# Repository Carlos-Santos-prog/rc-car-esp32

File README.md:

# RC Car ESP32 🏎️

**Vehículo RC de combate con seguimiento de línea, controlado por ESP32.**

Proyecto final del **Laboratorio de Electrónica II** del Instituto Tecnológico de las Américas (ITLA). Este repositorio reúne el diseño electrónico completo —esquemático, PCB, BOM y documentación— y servirá también como base para el firmware del vehículo.

---

## 📋 Descripción

El carrito combina dos modos de operación:

- **Seguidor de línea:** dos sensores ópticos CNY70 detectan el trazado y el ESP32 corrige la trayectoria en tiempo real.
- **Funciones de batalla:** servos para barrera y pala, luces direccionales intermitentes y bocina, pensados para competencias entre vehículos.

La etapa de potencia maneja **cuatro motores DC de forma independiente** mediante cuatro puentes H con MOSFETs, aislados por optoacopladores para proteger la lógica del ESP32.

## ✨ Características

- Control central con **ESP32 DevKitC V4**.
- **4 puentes H** independientes (IRF3205 + IRF9540N) para tracción 4WD.
- Aislamiento de señal de los puentes H con **optoacopladores PC817**.
- **2 sensores de línea CNY70** para seguimiento de pista.
- **3 servos** (barrera, pala y dirección auxiliar).
- **Luces direccionales** izquierda/derecha e intermitentes.
- **Bocina** con amplificador de audio **TDA2003**.
- Fuentes reguladas para lógica y servos: **LM7805**, **LM317** y rieles de +15 V, +7.5 V, +5 V y +3.3 V.
- PCB de **2 capas**, **80 × 130 mm**, con conectores JST EH para periféricos.

## 🧩 Arquitectura de hardware

| Bloque | Componentes principales |
|---|---|
| Control lógico | ESP32-DevKitC, MMBT3904, resistencias de pull-up |
| Seguidor de línea | 2 × CNY70 |
| Puentes H | 4 × IRF3205 (N), 4 × IRF9540N (P), 6 × PC817 |
| Servos | 3 × conectores JST EH de 3 pines |
| Luces | LED direccionales e intermitentes |
| Audio | TDA2003 + parlante (conector BOCINA) |
| Alimentación | LM7805, LM317, LM317 ajustable, capacitores de filtrado |
| Conectores | Batería principal, batería auxiliar, 4 motores, 3 servos, bocina, LEDs |

## 📁 Estructura del repositorio

```text
.
├── electronic_design_kicad/          # Diseño electrónico (KiCad 10)
│   ├── ProyectoFinalCarrito2.kicad_pro
│   ├── ProyectoFinalCarrito2.kicad_sch
│   ├── ProyectoFinalCarrito2.kicad_pcb
│   ├── ProyectoFinalCarrito2.csv     # Lista de materiales (BOM)
│   ├── ProyectoFinalCarrito2-schematic.pdf
│   ├── fabrication-toolkit-options.json
│   ├── docs/
│   │   └── esp32_devkitC_v4_pinlayout.png
│   └── README.md
├── .gitignore
├── .gitattributes
├── LICENSE
└── README.md
```

## 🚀 Cómo abrir el proyecto

1. Instala **KiCad 10.0** o superior.
2. Abre `electronic_design_kicad/ProyectoFinalCarrito2.kicad_pro`.
3. Desde KiCad puedes revisar:
   - **Esquemático** → `ProyectoFinalCarrito2.kicad_sch`
   - **PCB** → `ProyectoFinalCarrito2.kicad_pcb`
   - **ERC/DRC** para validar el diseño antes de fabricar.

> Los archivos conservan el nombre original del proyecto (`ProyectoFinalCarrito2`) para no romper las referencias internas entre hoja, placa y proyecto en KiCad.

## 🏭 Fabricación

- La **BOM** está en `electronic_design_kicad/ProyectoFinalCarrito2.csv`.
- El **esquemático en PDF** está en `electronic_design_kicad/ProyectoFinalCarrito2-schematic.pdf`.
- Los Gerbers se pueden generar con el plugin **Fabrication Toolkit** usando la configuración incluida (`fabrication-toolkit-options.json`).

## 🗺️ Roadmap

- [x] Diseño electrónico (esquemático + PCB)
- [ ] Firmware del ESP32 (control de motores, sensores y servos)
- [ ] Validación del prototipo y ajuste de PID del seguidor de línea
- [ ] Diseño de carcasa / estructura 3D
- [ ] Documentación de montaje y pruebas

## 📄 Licencia

Este proyecto se distribuye bajo la licencia **MIT**. Consulta [LICENSE](LICENSE) para más detalles.

## 👤 Autor

**Carlos Alexander Arias Santos**
Instituto Tecnológico de las Américas (ITLA) — Laboratorio de Electrónica II

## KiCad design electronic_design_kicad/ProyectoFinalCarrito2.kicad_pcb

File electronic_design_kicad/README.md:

# Diseño electrónico — RC Car ESP32

Diseño completo en **KiCad 10.0** del vehículo RC de combate con seguimiento de línea basado en ESP32.

## Contenido

| Archivo | Descripción |
|---|---|
| `ProyectoFinalCarrito2.kicad_pro` | Proyecto KiCad (abrir este archivo) |
| `ProyectoFinalCarrito2.kicad_sch` | Esquemático |
| `ProyectoFinalCarrito2.kicad_pcb` | Placa de circuito impreso (2 capas, 80 × 130 mm) |
| `ProyectoFinalCarrito2.csv` | Lista de materiales (BOM) |
| `ProyectoFinalCarrito2-schematic.pdf` | Esquemático exportado a PDF |
| `fabrication-toolkit-options.json` | Configuración del plugin Fabrication Toolkit |
| `docs/esp32_devkitC_v4_pinlayout.png` | Pinout de referencia del ESP32 DevKitC V4 |

## Bloques del diseño

- **Control lógico / ESP32:** ESP32-DevKitC V4 y etapa de acoplamiento con transistores MMBT3904.
- **Seguidor de línea:** 2 sensores ópticos CNY70.
- **Puentes H:** 4 etapas independientes con IRF3205 / IRF9540N y aislamiento por PC817.
- **Funciones de batalla:** 3 servos, luces direccionales e intermitentes y bocina con TDA2003.
- **Alimentación:** LM7805, LM317 y rieles de +15 V, +7.5 V, +5 V y +3.3 V.

## Notas

- Los archivos conservan el nombre original del proyecto para mantener las referencias internas de KiCad.
- `ProyectoFinalCarrito2.kicad_prl` y `fp-info-cache` son archivos locales de KiCad y están excluidos del repositorio mediante `.gitignore`.
- Las copias de seguridad automáticas (`*-backups/`) se conservan localmente, pero no se versionan.
- Antes de fabricar, ejecuta **ERC** y **DRC** en KiCad y genera los Gerbers con Fabrication Toolkit.

## Cómo abrir

1. Abre KiCad 10.0 o superior.
2. Selecciona `ProyectoFinalCarrito2.kicad_pro`.
3. Revisa el esquemático y la PCB desde el administrador de proyectos.

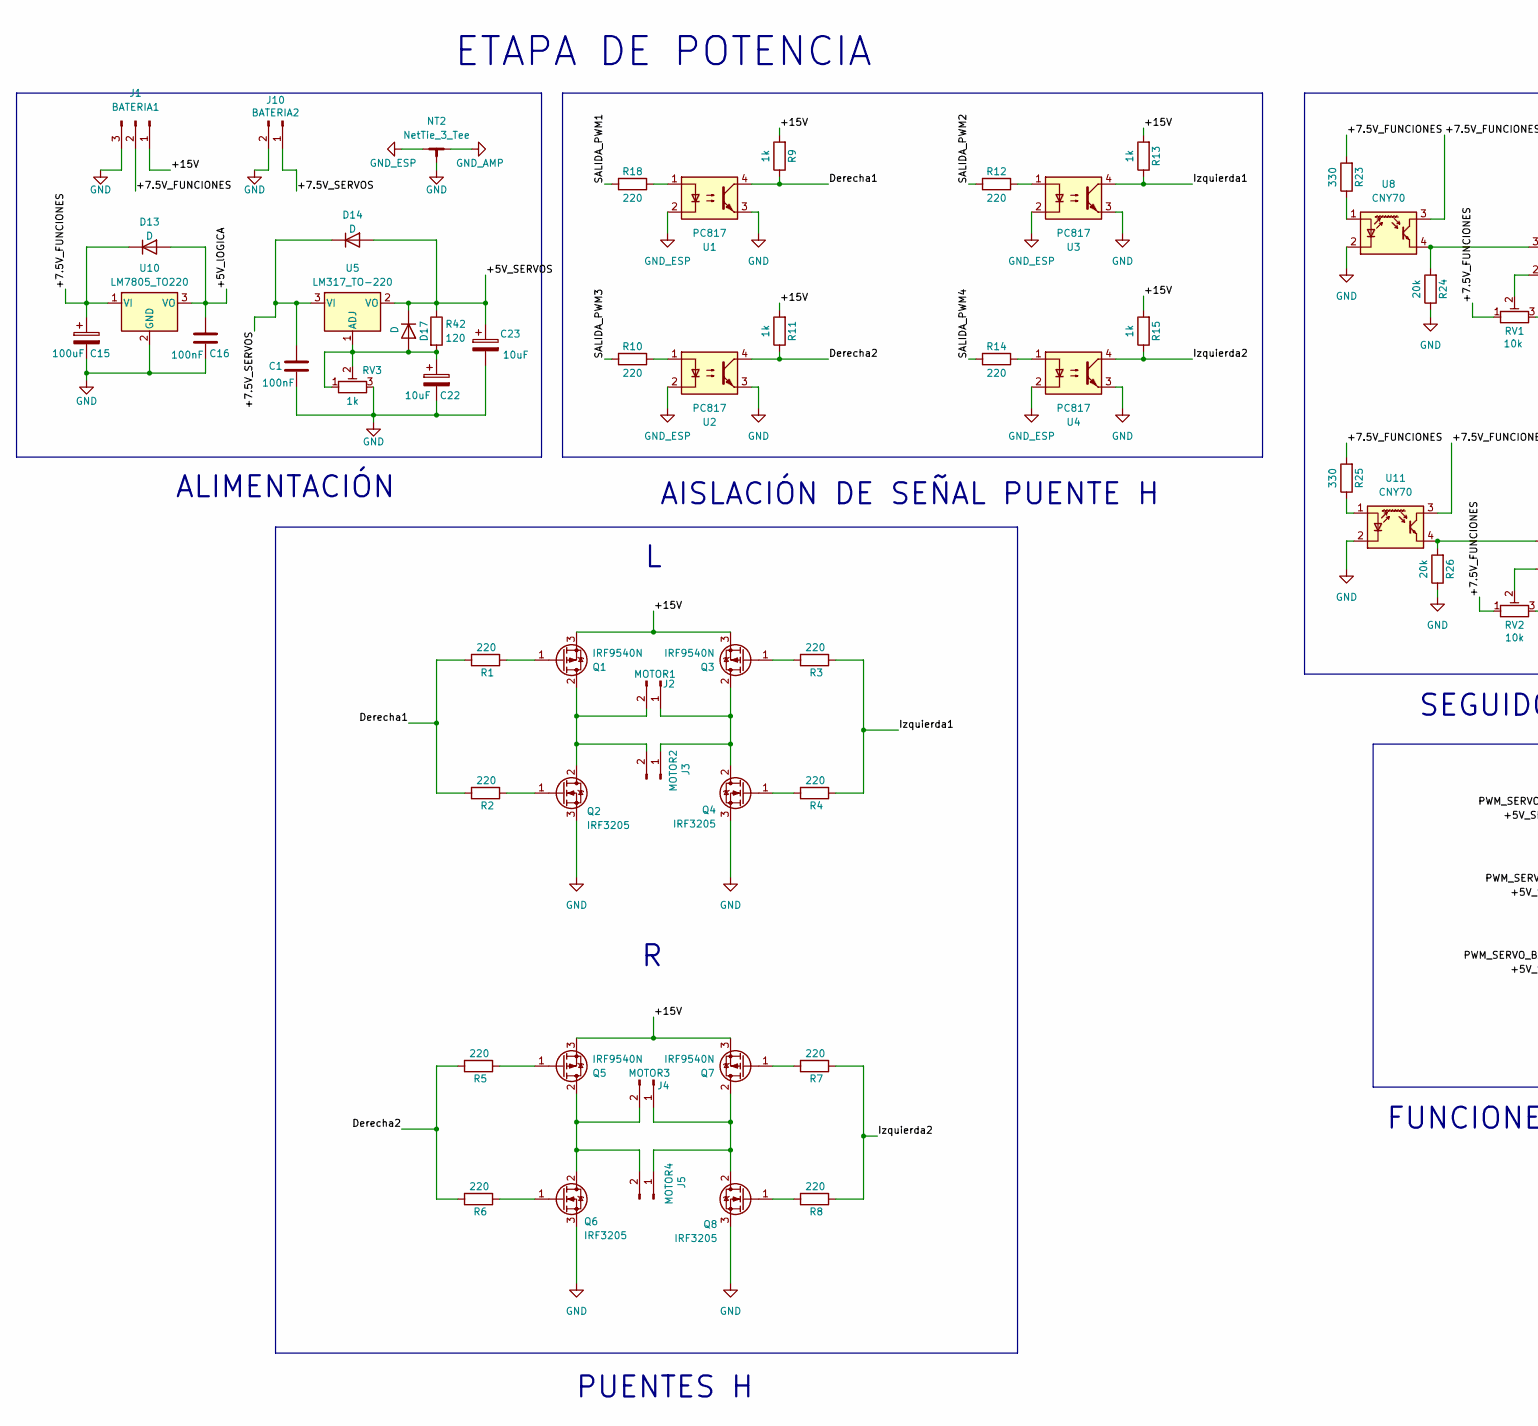
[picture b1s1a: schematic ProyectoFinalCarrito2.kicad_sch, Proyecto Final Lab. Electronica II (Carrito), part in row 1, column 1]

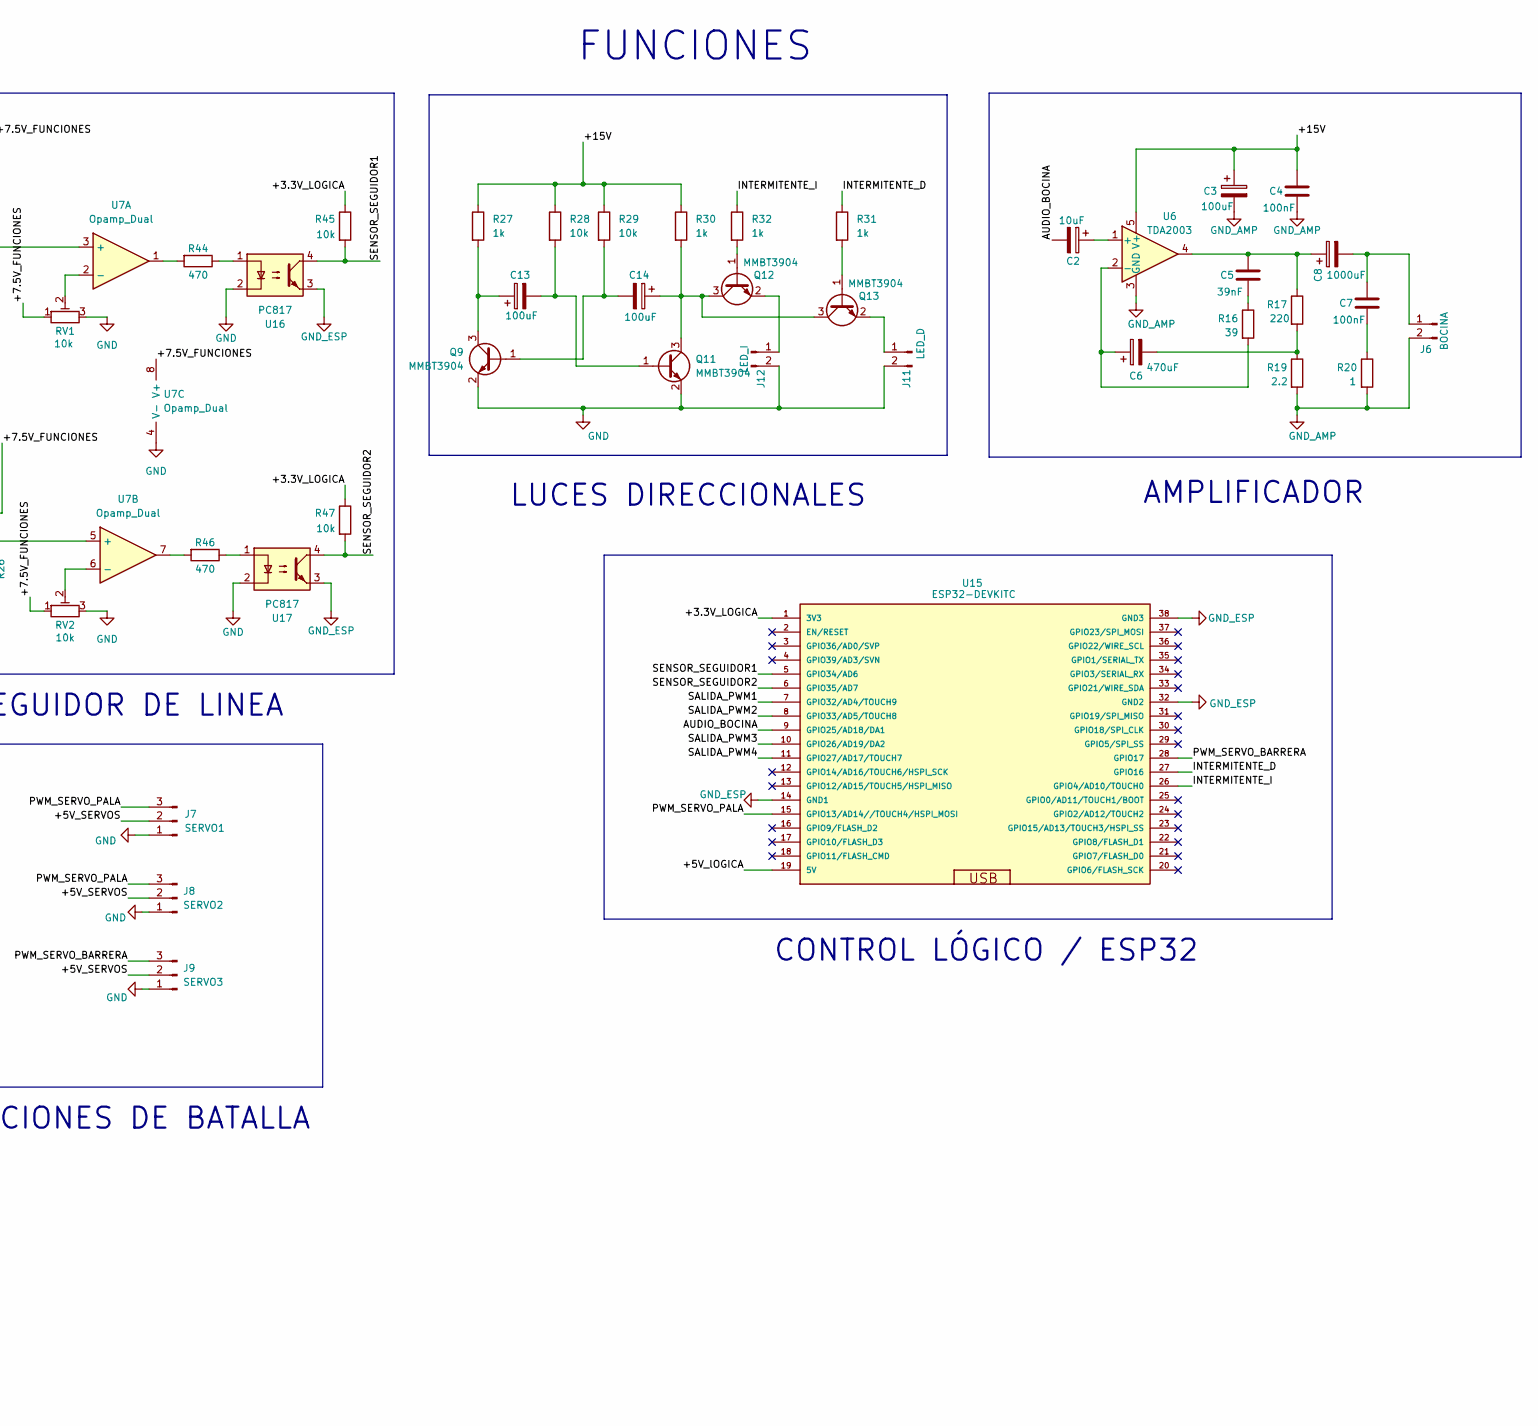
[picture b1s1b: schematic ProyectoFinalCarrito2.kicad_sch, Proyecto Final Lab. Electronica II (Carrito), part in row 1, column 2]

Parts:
C1, C4, C7, C16: 100nF; C_0805_2012Metric
C2, C22, C23: 10uF; CP_Radial_D5.0mm_P2.00mm
C3, C13, C14, C15: 100uF; CP_Radial_D8.0mm_P3.80mm
C5: 39nF; C_0805_2012Metric
C6: 470uF; CP_Radial_D10.0mm_P5.00mm
C8: 1000uF; CP_Radial_D10.0mm_P5.00mm
D13, D14, D17: D; D_SOD-123
J1: BATERIA1; JST_EH_B3B-EH-A_1x03_P2.50mm_Vertical
J2: MOTOR1; JST_EH_B2B-EH-A_1x02_P2.50mm_Vertical
J3: MOTOR2; JST_EH_B2B-EH-A_1x02_P2.50mm_Vertical
J4: MOTOR3; JST_EH_B2B-EH-A_1x02_P2.50mm_Vertical
J5: MOTOR4; JST_EH_B2B-EH-A_1x02_P2.50mm_Vertical
J6: BOCINA; JST_EH_B2B-EH-A_1x02_P2.50mm_Vertical
J7: SERVO1; JST_EH_B3B-EH-A_1x03_P2.50mm_Vertical
J8: SERVO2; JST_EH_B3B-EH-A_1x03_P2.50mm_Vertical
J9: SERVO3; JST_EH_B3B-EH-A_1x03_P2.50mm_Vertical
J10: BATERIA2; JST_EH_B2B-EH-A_1x02_P2.50mm_Vertical
J11: LED_D; JST_EH_B2B-EH-A_1x02_P2.50mm_Vertical
J12: LED_I; JST_EH_B2B-EH-A_1x02_P2.50mm_Vertical
NT2: NetTie_3_Tee; NetTie-3_SMD_Pad2.0mm
Q1, Q3, Q5, Q7: IRF9540N; TO-220-3_Vertical
Q2, Q4, Q6, Q8: IRF3205; TO-220-3_Vertical
Q9, Q11, Q12, Q13: MMBT3904; SOT-23
R1, R2, R3, R4, R5, R6, R7, R8: 220; R_Axial_DIN0207_L6.3mm_D2.5mm_P10.16mm_Horizontal
R9, R11, R13, R15: 1k; R_Axial_DIN0207_L6.3mm_D2.5mm_P10.16mm_Horizontal
R10, R12, R14, R17, R18: 220; R_0805_2012Metric
R16: 39; R_0805_2012Metric
R19: 2.2; R_0805_2012Metric
R20: 1; R_1206_3216Metric
R23, R25: 330; R_0805_2012Metric
R24, R26: 20k; R_0805_2012Metric
R27, R30, R31, R32: 1k; R_0805_2012Metric
R28, R29, R45, R47: 10k; R_0805_2012Metric
R42: 120; R_0805_2012Metric
R44, R46: 470; R_0805_2012Metric
RV1, RV2: 10k; Potentiometer_Bourns_3266W_Vertical
RV3: 1k; Potentiometer_Bourns_3266W_Vertical
U1, U2, U3, U4, U16, U17: PC817; DIP-4_W7.62mm
U5: LM317_TO-220; TO-220-3_Vertical
U6: TDA2003; TO-220-5_P3.4x3.7mm_StaggerOdd_Lead3.8mm_Vertical
U7: Opamp_Dual; SOIC-8_3.9x4.9mm_P1.27mm
U8, U11: CNY70; Vishay_CNY70
U10: LM7805_TO220; TO-220-3_Vertical
U15: ESP32-DEVKITC

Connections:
/+3.3V_LOGICA: R45.1, R47.1, U15.1 (3V3)
/+5V_SERVOS: C23.1, D14.2 (A), D17.1 (K), J7.2, J8.2, J9.2, R42.1, U5.2 (VO)
/+5V_lOGICA: C16.2, D13.2 (A), U10.3 (VO), U15.19 (5V)
/+7.5V_FUNCIONES: C15.1, D13.1 (K), J1.2, R23.2, R25.2, RV1.1, RV2.1, U7.8 (V+), U8.3 (C), U10.1 (VI), U11.3 (C)
/+7.5V_SERVOS: C1.2, D14.1 (K), J10.1, U5.3 (VI)
/+15V: C3.1, C4.2, J1.1, Q1.3 (S), Q3.3 (S), Q5.3 (S), Q7.3 (S), R9.2, R11.2, R13.2, R15.2, R27.1, R28.1, R29.1, R30.1, U6.5 (V+)
/AUDIO_BOCINA: C2.2, U15.9 (GPIO25/AD18/DA1)
/Derecha1: R1.2, R2.2, R9.1, U1.4
/Derecha2: R5.2, R6.2, R11.1, U2.4
/INTERMITENTE_D: R31.1, U15.27 (GPIO16)
/INTERMITENTE_I: R32.1, U15.26 (GPIO4/AD10/TOUCH0)
/Izquierda1: R3.1, R4.1, R13.1, U3.4
/Izquierda2: R7.1, R8.1, R15.1, U4.4
/PWM_SERVO_BARRERA: J9.3, U15.28 (GPIO17)
/PWM_SERVO_PALA: J7.3, J8.3, U15.15 (GPIO13/AD14//TOUCH4/HSPI_MOSI)
/SALIDA_PWM1: R18.2, U15.7 (GPIO32/AD4/TOUCH9)
/SALIDA_PWM2: R12.2, U15.8 (GPIO33/AD5/TOUCH8)
/SALIDA_PWM3: R10.2, U15.10 (GPIO26/AD19/DA2)
/SALIDA_PWM4: R14.2, U15.11 (GPIO27/AD17/TOUCH7)
/SENSOR_SEGUIDOR1: R45.2, U15.5 (GPIO34/AD6), U16.4
/SENSOR_SEGUIDOR2: R47.2, U15.6 (GPIO35/AD7), U17.4
GND: C1.1, C15.2, C16.1, C22.2, C23.2, J1.3, J7.1, J8.1, J9.1, J10.2, J11.2, J12.2, NT2.3, Q2.3 (S), Q4.3 (S), Q6.3 (S), Q8.3 (S), Q9.2 (E), Q11.2 (E), R24.1, R26.1, RV1.3, RV2.3, RV3.3, U1.3, U2.3, U3.3, U4.3, U7.4 (V-), U8.2 (K), U10.2 (GND), U11.2 (K), U16.2, U17.2
GND_AMP: C3.2, C4.1, J6.2, NT2.2, R19.2, R20.2, U6.3 (GND)
GND_ESP: NT2.1, U1.2, U2.2, U3.2, U4.2, U15.14 (GND1), U15.32 (GND2), U15.38 (GND3), U16.3, U17.3
unnamed: C5.1, R16.1
unnamed: C5.2, C8.1, R17.1, U6.4
unnamed: C6.2, R17.2, R19.1
unnamed: C7.1, R20.1
unnamed: C22.1, D17.2 (A), R42.2, RV3.1, RV3.2, U5.1 (ADJ)
unnamed: J2.1, J3.1, Q3.2 (D), Q4.2 (D)
unnamed: J2.2, J3.2, Q1.2 (D), Q2.2 (D)
unnamed: J4.1, J5.1, Q7.2 (D), Q8.2 (D)
unnamed: J4.2, J5.2, Q5.2 (D), Q6.2 (D)
unnamed: C7.2, C8.2, J6.1
unnamed: J11.1, Q13.2 (E)
unnamed: J12.1, Q12.2 (E)
unnamed: Q1.1 (G), R1.1
unnamed: Q2.1 (G), R2.1
unnamed: Q3.1 (G), R3.2
unnamed: Q4.1 (G), R4.2
unnamed: Q5.1 (G), R5.1
unnamed: Q6.1 (G), R6.1
unnamed: Q7.1 (G), R7.2
unnamed: Q8.1 (G), R8.2
unnamed: C14.2, Q9.1 (B), R29.2
unnamed: C13.1, Q9.3 (C), R27.2
unnamed: C13.2, Q11.1 (B), R28.2
unnamed: C14.1, Q11.3 (C), Q12.3 (C), Q13.3 (C), R30.2
unnamed: Q12.1 (B), R32.2
unnamed: Q13.1 (B), R31.2
unnamed: R10.1, U2.1
unnamed: R12.1, U3.1
unnamed: R14.1, U4.1
unnamed: R18.1, U1.1
unnamed: R44.1, U16.1
unnamed: R44.2, U7.1
unnamed: R46.1, U17.1
unnamed: R46.2, U7.7
unnamed: C2.1, U6.1 (+)
unnamed: C6.1, R16.2, U6.2 (-)
unnamed: R24.2, U7.3 (+), U8.4 (E)
unnamed: RV1.2, U7.2 (-)
unnamed: RV2.2, U7.6 (-)
unnamed: R23.1, U8.1 (A)
unnamed: R25.1, U11.1 (A)
unnamed: R26.2, U7.5 (+), U11.4 (E)

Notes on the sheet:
SEGUIDOR DE LINEA
FUNCIONES DE BATALLA
LUCES DIRECCIONALES
AISLACIÓN DE SEÑAL PUENTE H
CONTROL LÓGICO / ESP32
ALIMENTACIÓN
PUENTES H
AMPLIFICADOR
FUNCIONES
ETAPA DE POTENCIA

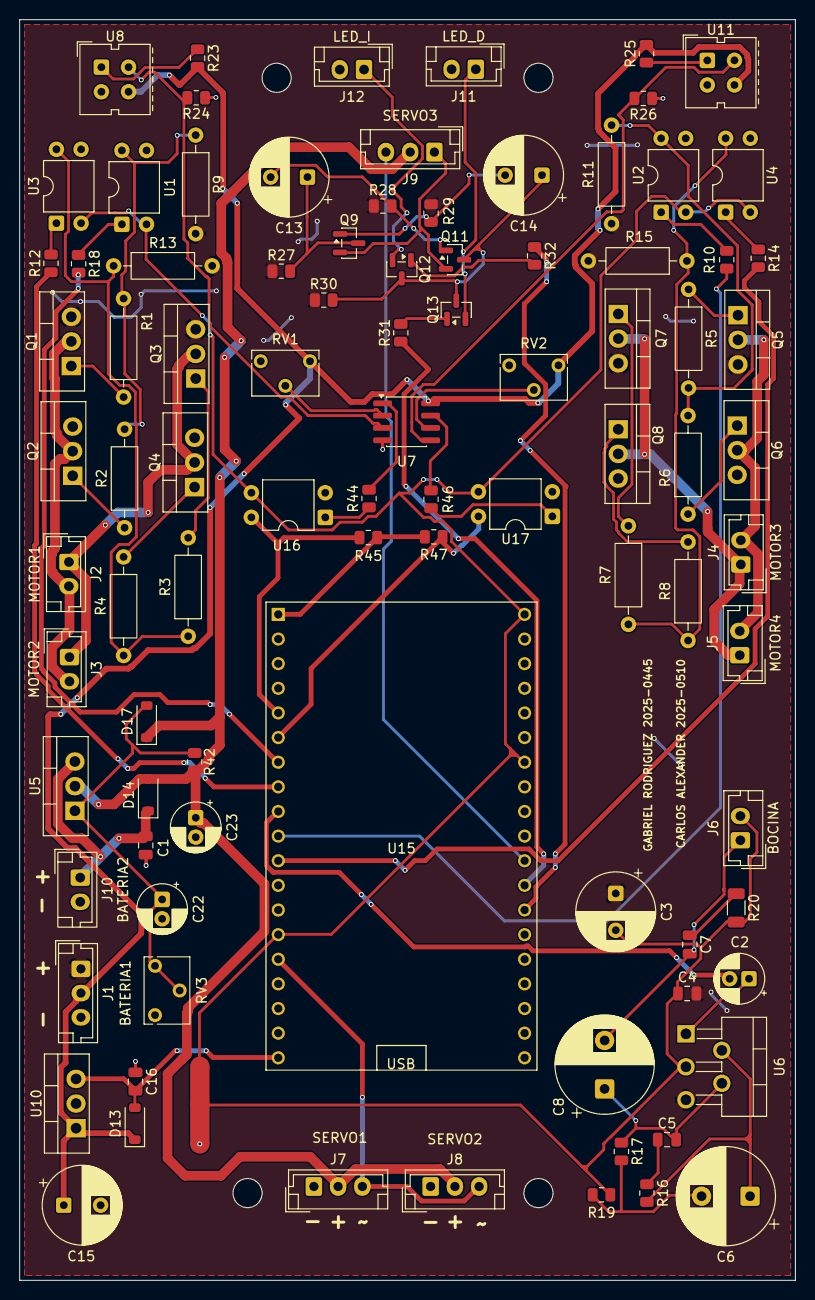
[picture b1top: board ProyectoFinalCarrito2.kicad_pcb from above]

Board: 2 copper layers, 80.0 x 130.0 mm, 93 parts (0 on the bottom side), 66 nets.

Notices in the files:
README.md:
License: MIT
